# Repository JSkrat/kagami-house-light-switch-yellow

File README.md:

# kagami-house-light-switch-yellow
Firmware for the light switch lv 1.0 yellow board (RGB led controller + buzzer)

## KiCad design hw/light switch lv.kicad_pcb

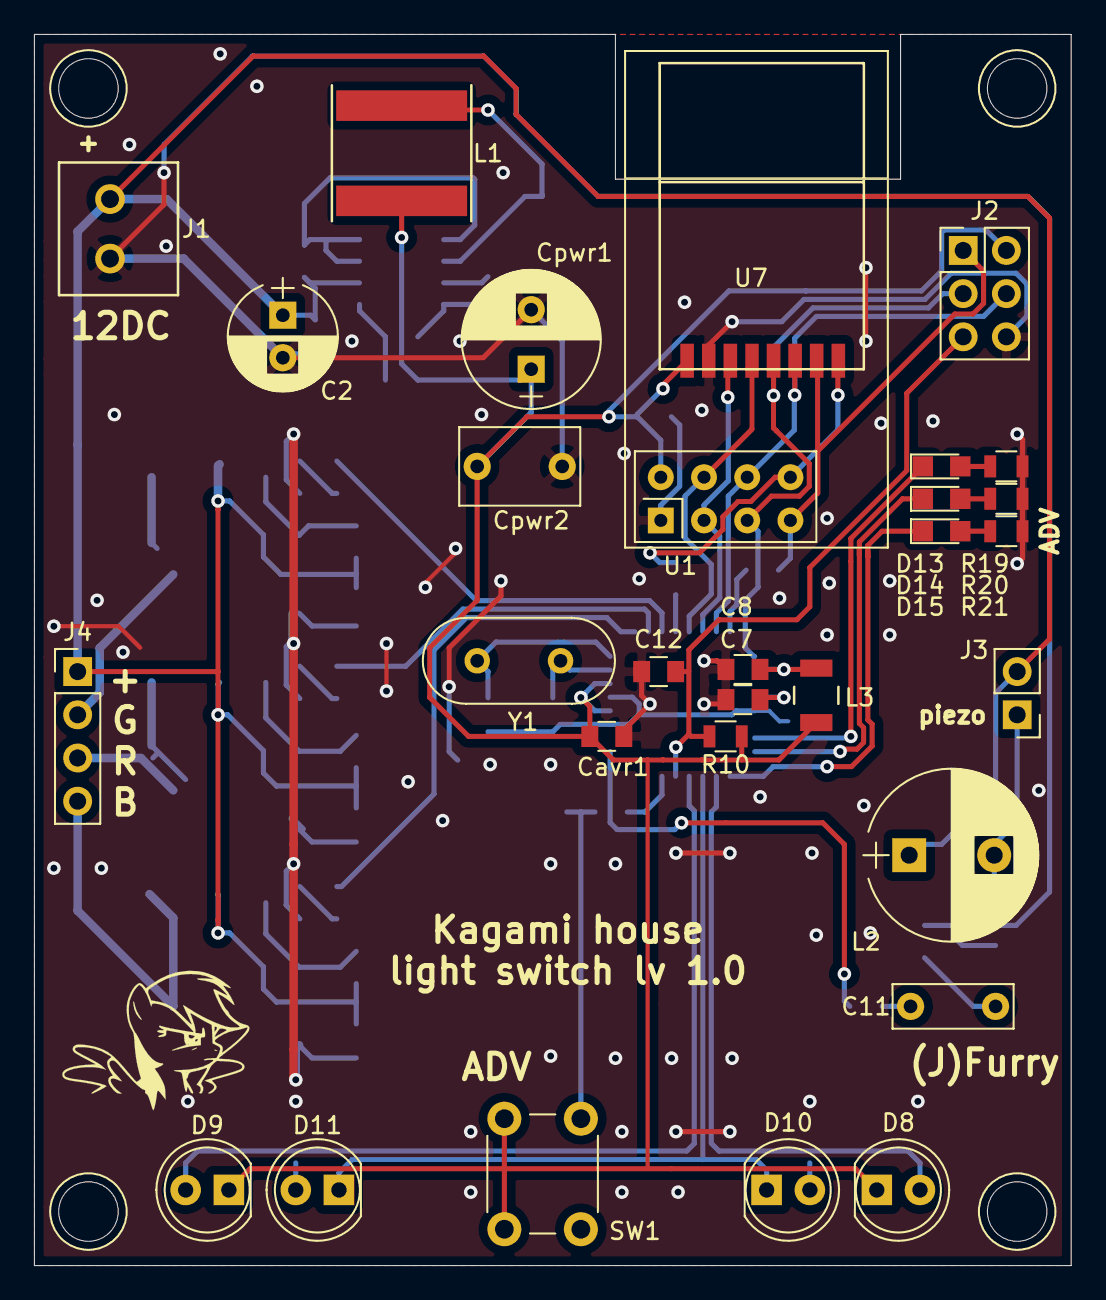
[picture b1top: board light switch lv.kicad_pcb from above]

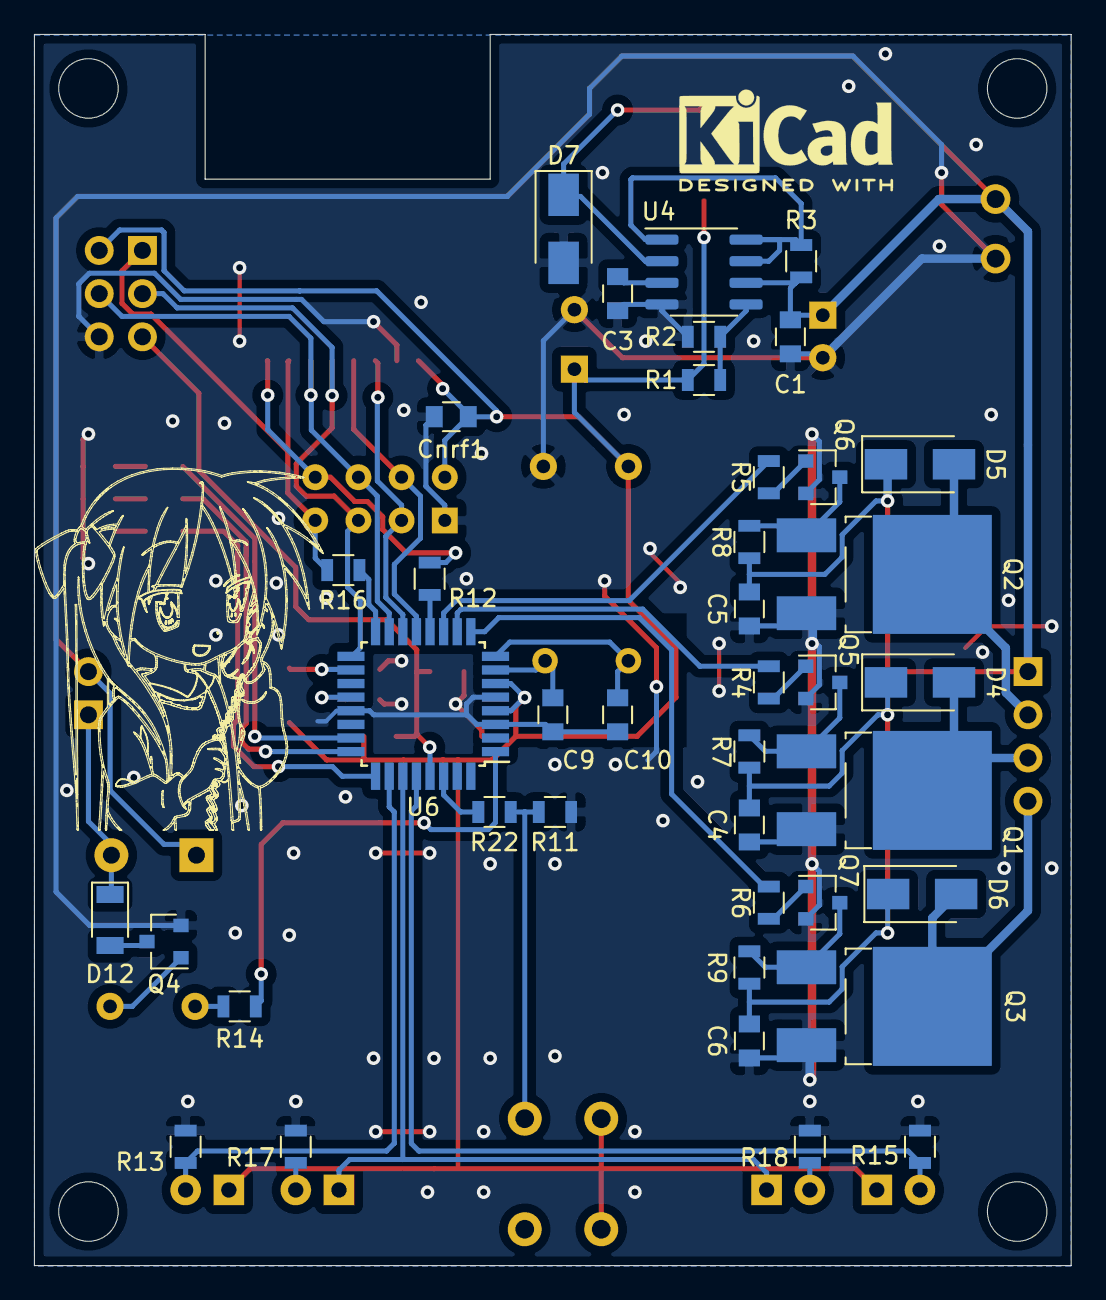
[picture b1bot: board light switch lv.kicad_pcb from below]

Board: 2 copper layers, 61.0 x 72.4 mm, 70 parts (40 on the bottom side), 50 nets.

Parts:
C1, C4, C5, C6, C7, C8, C12: 100n; C_0805
C2: 100u; CP_Radial_D6.3mm_P2.50mm
C3: 470p; C_0805
C9, C10: 22p; C_0805
C11: 100n; C_Rect_L7.0mm_W2.5mm_P5.00mm
Cavr1: 100n; C_0805
Cnrf1: 100n; C_0805
Cpwr1: 470u; CP_Radial_D8.0mm_P3.50mm
Cpwr2: 100n; C_Rect_L7.0mm_W4.5mm_P5.00mm
D4, D5, D6, D7: SS16; D_SMA
D8, D9: D_Photo; LED_D5.0mm
D10, D11: LED; LED_D5.0mm
D12: 1N4148; D_1206
D13, D14: LED; LED_0805
D15: ADV; LED_0805
J1: DC in; 15EDGVC-3.5_2
J2: AVR-ISP-6; Pin_Header_Straight_2x03_Pitch2.54mm
J3: Conn_01x02_Male; Pin_Header_Straight_1x02_Pitch2.54mm
J4: Conn_01x04_Male; Pin_Header_Straight_1x04_Pitch2.54mm
L1: 220uH SND0705-221M; Inductor_Taiyo-Yuden_NR-80xx
L2: 10mH; CP_Radial_D10.0mm_P5.00mm
L3: 10uH; Neosid_Inductor_SM-NE30_SMD1210
Q1, Q2, Q3: Q_NMOS_GDS; TO-252-2_Rectifier
Q4, Q5, Q6, Q7: BC847; SOT-23
R1: 1k2; R_0805
R2: 2k; R_0805
R3: 0.33; R_0805
R4, R5, R6, R7, R8, R9, R10, R11, R13, R15: 10k; R_0805
R12, R16, R22: 22; R_0805
R14: 1k; R_0805
R17, R18, R19, R20, R21: 220; R_0805
SW1: SW_Push; SW_PUSH_6mm_h4.3mm
U1: NRF24L01_Breakout; nRF24L01_Breakout
U4: MC34063AD; SOIC-8_3.9x4.9mm_P1.27mm
U6: ATmega88PA-AU; TQFP-32_7x7mm_P0.8mm
U7: NRF24L01_Breakout; nRF24L01_SMD
Y1: Crystal; Crystal_HC18-U_Vertical

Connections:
/+3.3: Cavr1.1, Cnrf1.1, Cpwr1.1, Cpwr2.1, D8.1, D9.1, J2.2, L1.2, L3.1, R2.1, R10.1, SW1.2, U1.2, U6.4, U6.6, U7.2
/+3.3a: C8.1, L3.2, U6.18
/+12: C1.1, C2.1, C4.1, C5.1, C6.1, D4.1, D5.1, D6.1, J1.2, J3.2, J4.1, L2.1, R3.2, R7.1, R8.1, R9.1, U4.6
/L1: D13.1, U6.23
/L2: D14.1, U6.24
/adv: D15.1, U6.25
/adv_on: R11.1, R22.1, SW1.1
/aref: C7.1, U6.20
/blue: R6.2, U6.9
/blue_out: D6.2, J4.4, Q3.2
/buzzer: R14.2, U6.1
/gnd: C1.2, C2.2, C3.2, C4.2, C5.2, C6.2, C7.2, C8.2, C9.2, C10.2, C12.2, Cavr1.2, Cnrf1.2, Cpwr1.2, Cpwr2.2, D7.2, J1.1, J2.6, Q1.3, Q2.3, Q3.3, Q4.2, Q5.2, Q6.2, Q7.2, R1.2, R11.2, R13.2, R15.2, R17.2, R18.2, R19.2, R20.2, R21.2, U1.1, U4.4, U6.3, U6.5, U6.21, U7.1
/green: R5.2, U6.11
/green_out: D5.2, J4.2, Q2.2
/ph1: D8.2, R13.1, U6.26
/ph2: D9.2, R15.1, U6.28
/q1: C9.1, U6.7, Y1.2
/q2: C10.1, U6.8, Y1.1
/red: R4.2, U6.10
/red_out: D4.2, J4.3, Q1.2
/rst: C12.1, J2.5, R10.2, U6.29
/sensor_light: D10.1, D11.1, U6.27
/tr_ce: U1.3, U6.14, U7.3
/tr_csn: U1.4, U6.13, U7.4
/tr_irq: R12.1, U1.8, U7.8
/tr_miso: J2.1, R16.1, U1.7, U7.7
/tr_mosi: J2.4, U1.6, U6.15, U7.6
/tr_sck: J2.3, U1.5, U6.17, U7.5
unnamed: C3.1, U4.3
unnamed: C11.1, Q4.1
unnamed: C11.2, R14.1
unnamed: D7.1, L1.1, U4.2
unnamed: D10.2, R17.1
unnamed: D11.2, R18.1
unnamed: D12.1, J3.1, L2.2
unnamed: D12.2, Q4.3
unnamed: D13.2, R19.1
unnamed: D14.2, R20.1
unnamed: D15.2, R21.1
unnamed: Q1.1, Q5.3, R7.2
unnamed: Q2.1, Q6.3, R8.2
unnamed: Q3.1, Q7.3, R9.2
unnamed: Q5.1, R4.1
unnamed: Q6.1, R5.1
unnamed: Q7.1, R6.1
unnamed: R1.1, R2.2, U4.5
unnamed: R3.1, U4.1, U4.7, U4.8
unnamed: R12.2, U6.12
unnamed: R16.2, U6.16
unnamed: R22.2, U6.30

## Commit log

2021-08-19 add kagami core submlodule
2021-08-19 project initial commit
2021-08-19 add core configuration
2021-08-29 add code, move core to subfolder
2021-08-29 make leds off at start add ui make ui heartbeat and transmission indication init timer structures, fix interrupt
2021-08-29 increase frequency of led pwm alter heartbeat update leds state on status switch
2021-08-29 add hardware part
2021-08-29 add case and stepdown calculator table
2021-08-29 make heartbeat as fast as possible so transmission led blinks are visible
